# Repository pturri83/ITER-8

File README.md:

# DB6502 - Dawid Buchwald's 6502 Computer

This repository contains all the work in progress during my build of Ben Eater's inspired 6502 8-bit computer similar to typical machines of the early 1980s. If you haven't seen Ben's videos, I would strongly suggest you start there:

[Ben Eater's 6502 project](https://eater.net/6502)

As stated above, this build is not 100% compatible with what Ben had done - and for a reason, described in next section.

If I had to explain shortly "what it is", the answer would be: simple, yet easy to expand, 8-bit CPU based computer designed and built with one goal only: to use it as a learning and tinkering platform to understand how computers really work. You can use it for simple things like understanding buses, clock cycles, instruction execution, but it also demonstrates more complex concepts like interrupts, interfaces to external components and device handling. More on that below. Everything, hopefully, is simple enough to wrap your head around by one person in couple of weeks.

## Why build something different

[Ben's videos](https://www.youtube.com/playlist?list=PLowKtXNTBypFbtuVMUVXNR0z1mu7dp7eH) on 6502 computer are absolutely awesome - it's one of the best sources in the whole Internet explaining how any computer works. The build he introduced is probably sufficient for most of the things you might ever want to build, and yet I decided to deviate from his design.

The rationale behind this project is pretty simple - the best way to test your understanding of certain subject is to try to expand on what you have learned. You never know if you understood something until you test it by introducing changes to original design - and I used this approach in this project to learn a lot. It was my first proper electronics project, so I would like to apologize for any mistakes. If you think something is off or could have been done differently - please go ahead and raise issue for the repo! All improvements are welcome!

## Why would you bother using DB6502 instead of BE6502

Basically, it gives you almost all the flexibility of Ben's buid without the hassle of breadboard connections for the critical components. You can still run all of Ben's programs (using second VIA port), but the days of looking for loose wire between RAM and CPU are over :) You can, obviously, still experiment with peripherals and breadboard connections using extension port and second VIA.

On top of that you get additional features like extra screen (via onboard connector), keyboard for more versatile input and finally all-in-one serial over USB terminal. You also get easy to use software ready to be installed on the machine to jumpstart your tinkering. When using bootloader you don't even have to flash the EEPROM more than once!

**Important note:** All of the content here is, and always will be open source and free to use, and I don't intend to make any profit out of it. The only way I get anything at all (and it's only small commission to be used for future PCBWay orders) is when you order my boards from PCBWay using the links posted below, but you are welcome to grab these gerber files and order the boards from another provider, or even from PCBWay, just by uploading gerbers to your account, if you don't want me to get the commission :)

## What is different

Compared to Ben's 6502 build I introduced the following changes:

1. Added [automatic power-up reset circuitry](Schematics/README.md#automatic-power-on-reset),
2. Changed [address decoder logic](Schematics/README.md#address-decoder-change) (**very important from compatibility perspective**),
3. Changed [LCD interface](Schematics/README.md#lcd-interface-change) from 8-bit to 4-bit (**very important from compatibility perspective**),
4. Added [additional VIA chip](Schematics/README.md#extra-via-chip) to provide easy expansion of the system,
5. Added [ACIA chip for serial communication](Schematics/README.md#extra-acia-chip-for-serial-communication),
6. Added (**optional - more on that later**) [USB-UART interface](Schematics/README.md#extra-usb-uart-interface-chip) for easy connectivity with PC,
7. Added [PS/2 keyboard port and ATtiny4313-based keyboard controller](Schematics/README.md#ps2-keyboard-interface-and-attiny4313-based-controller) to provide proper replacement for five pushbuttons in Ben's design,
8. Added [expansion port](Schematics/README.md#expansion-port) (not really deviation from Ben's build, save for one detail - unlike Ben's build, my version can support various interrupt sources, including the expansion port),
9. Modified [clock module](Schematics/README.md#modified-clock-module) (external),
10. Changed [compilator from VASM to CC65](Schematics/README.md#migration-from-vasm-to-cc65),
11. Added [simple way to choose clock source](Schematics/README.md#clock-input).

You might be wondering if this means that you can't run Ben's programs on DB6502 - and the answer is **YES YOU CAN**. Indeed, some changes to the code are necessary, but thanks to the additional VIA chip and with some changes to the addressing mode you can run any program from Ben's videos. If you want to use LCD in 8-bit mode, you can also use the additional VIA for it, ignoring the built-in LCD connector.

By the way, the opposite is also true - **you can compile and run my programs on Ben's computer**. There are special compilation flags that enable usage of Ben's address decoder. I will describe this in more detail in software section.

Detailed description and rationale for each change is discussed in [Schematics README](Schematics/README.md).

## Getting started

Okay, so it should be pretty clear what this project is about, so how to start playing with it? That really depends on what you decide to do:

- Stick with BE6502 and just use subset of provided software (either to install it in EEPROM, or just use it as reference for your own hacking),
- Build your own breadboard design based on this one with any modifications you can think of,
- Order PCBs of DB6502, solder the components and run provided software to see how it works and get started with your own designs.

To start from scratch it's actually easiest to select last option - after some waiting you will end up having pretty solid base to extend your design on.

### Using provided software with BE6502

If you decide to go down that route, head straight to the `Software` folder, where you will find several programs either identical or similar to what Ben has shown in his videos, but built with much more versatile toolchain.

If you want to read more, go ahead and read [Software folder](Software/README.md) section. Make sure to check out the [building software](Software/README.md#building-software) subsection, as it explains how to compile programs to run on BE6502 directly.

### Build your own breadboard design

Maybe you have already started expanding on Ben's build, or maybe you are just considering it now. If you want to check out how I did certain things, jump right into `Schematics` [folder](Schematics/README.md), where you will find KiCAD projects for all the components used in this project. Obviously the most important one is the `65C02_Computer` project, but there are some additional goodies there.

**Please note:** This part is not very well documented, I have assumed that anybody willing to dig into these schematics already knows how to read them.

Most of the decisions made during the schematic design were explained above. Justification for anything not covered here can be probably found in the [invaluable 6502 primer](http://wilsonminesco.com/6502primer/).

### Using my PCB design

This will be explained in the most detail, obviously. Start with getting [the PCBs](Schematics/README.md#ordering-pcb). **Please note:** clock module is entirely optional, but really useful for single stepping or slow clocking required by Ben Eater's design of Arduino Mega based bus analyzer. As explained in number of places here, you can either order PCBs from PCBWay directly or use your manufacturer of choice - it should have no impact on the final result.

## What's in the repo

Everything, basically. Schematics of the 6502 board, modified clock module, address decoder and other circuits I built during the project. Arduino sketches I used for debugging and simple programs used to test different features.

And, last but not least, full set of sample programs to follow Ben's videos on DB6502 plus my own bootloader/OS. The last two things are coming soon :)

### `Arduino` folder

There are several sketches there, and their full description is available is [separate README](Arduino/README.md).

### `AVR` folder

There are several projects there, used to experiment with pure `avr-gcc` development for Atmel AVR chips. While it has been interesting adventure that I plan to explore further in the future, it was easier to stick to standard Arduino tools for now and simply restructure code to work there.

### `Datasheets` folder

All the datasheets I used when designing DB6502, attached for reference.

### `Schematics` folder

All the KiCAD schematics for the 6502 computer, modified clock module and several others:

- 65C02_Computer - main schematic, including PCB design for DB6502 computer,
- Clock_module - schematic for the modified clock module, including PCB design,
- 555_troubleshoot - schematic of circuit used in [troubleshooting of clock module monostable noise issue](https://www.reddit.com/r/beneater/comments/edp1ls/noise_issue_in_monostable_mode_of_ben_eaters/),
- Address_decoder_basic - schematic of Ben Eater's address decoder for 6502 project,
- Address_decoder_basic_v2 - slightly modified version of the above,
- Address_decoder_extended - schematic of my own address decoder, used in the DB6502 computer.

There is dedicated [README](Schematics/README.md) in the folder, containing all the build-related details.

### `Software` folder

This one is the most important folder, as it contains range of different programs to play with the 6502 computer. Large subset of this programs can be built for Ben Eater's version of the 6502 computer without any changes. Some of them, however, use features available only in DB6502, like ACIA or keyboard connector. These can still be ran on Ben Eater's 6502 computer, assuming that compatible hardware is added to it.

The `Software` folder is currently divided into four main parts:

- `build` - temporary folder where all the build artifacts are created, including ROM binaries to be uploaded to EEPROM,
- `common` - common sources: include files with common constants, sources with shared function, configuration files for different address decoder logic modes, shared makefile used by all projects and small python script to optimize size of loadable modules,
- `rom` - set of projects used to create various ROM images to follow Ben's videos, test different features of the board and **some day** complete operating system for the computer,
- `load` - set of project containing loadable modules. These can be uploaded at runtime, without the need to flash the EEPROM. Basic bootloader is required, obviously, and the usage instructions are provided below.

There is also one "master" makefile located directly in the `Software` folder - it will build all the projects in `rom` and `load` subfolders.

There is dedicated [README](Software/README.md) in the folder, containing all the software-related details.

## Credits

This project would not be possible if not inspiration, support and help from many, many people:

- [Ben Eater](https://eater.net) - his videos inspired me to learn all this,
- [Dirk Grappendorf](https://grappendorf.net) - awesome documentation of his own 6502 project,
- [Wilson Mines Co.](http://wilsonminesco.com) - the best source of 6502-related information,
- [Dane Creek Photography](https://github.com/danecreekphotography) - for all his support and test driving the project,
- [u/transistorykris](https://www.reddit.com/user/transitorykris/) - his [KrisOS](https://github.com/transitorykris/krisos) is a great inspiration for my own OS development,
- [r/beneater community](https://www.reddit.com/r/beneater/) - for all the great ideas, feedback, creative spirit and exceptional support.

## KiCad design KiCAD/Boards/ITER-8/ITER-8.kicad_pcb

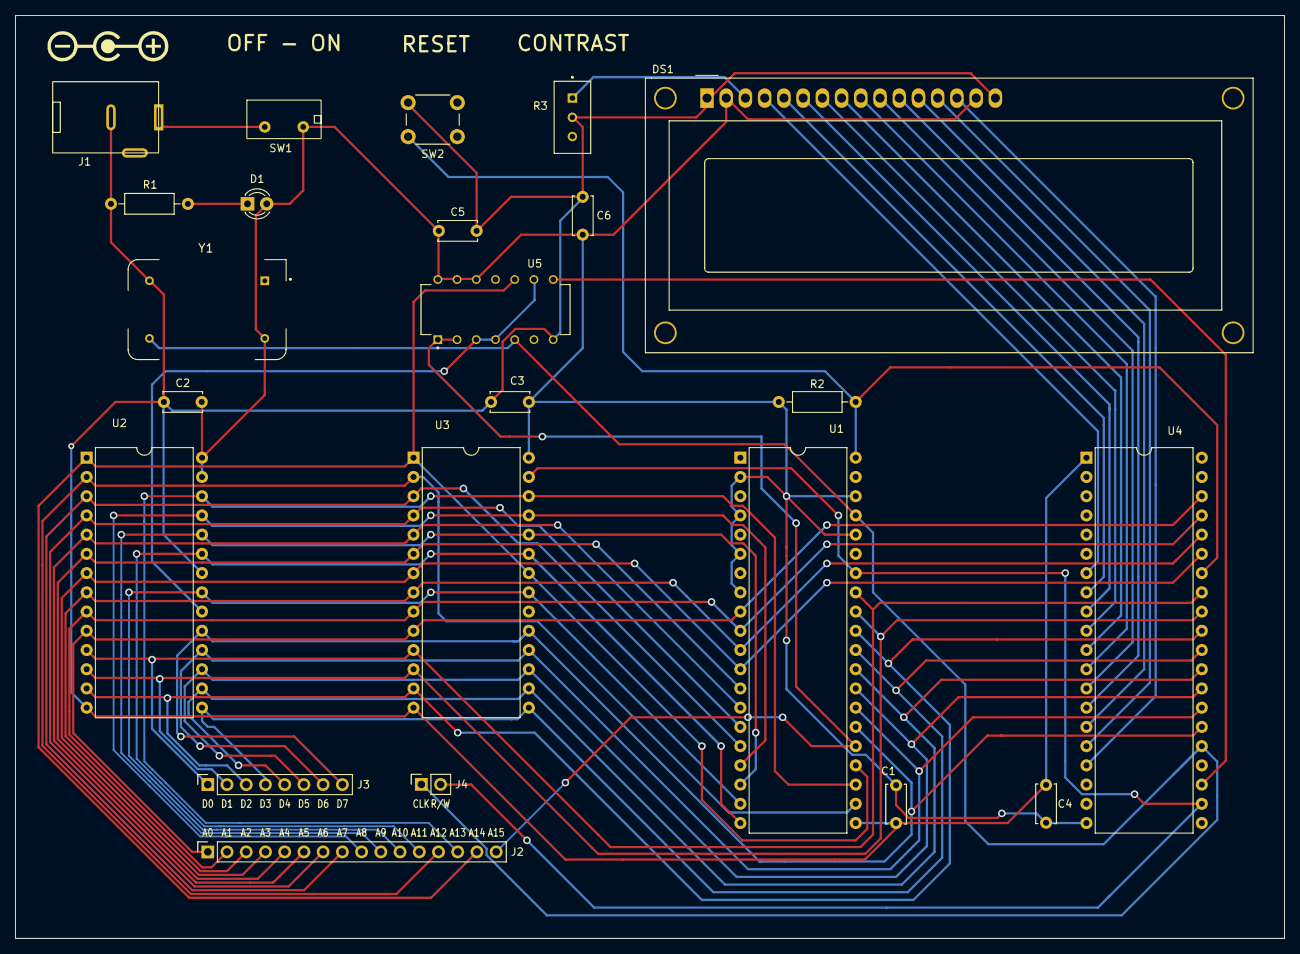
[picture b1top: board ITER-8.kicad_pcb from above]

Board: 2 copper layers, 167.6 x 121.9 mm, 23 parts (0 on the bottom side), 46 nets.

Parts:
C1, C2, C3, C4, C5, C6: 100n; C_Disc_D5.0mm_W2.5mm_P5.00mm
D1: LED; LED_D3.0mm
DS1: LCD-016M002B; WC1602A
J1: DC-005
J2: Conn_01x16; PinSocket_1x16_P2.54mm_Vertical
J3: Conn_01x08; PinSocket_1x08_P2.54mm_Vertical
J4: Conn_01x02; PinSocket_1x02_P2.54mm_Vertical
R1: 150R; R_Axial_DIN0207_L6.3mm_D2.5mm_P10.16mm_Horizontal
R2: 1k; R_Axial_DIN0207_L6.3mm_D2.5mm_P10.16mm_Horizontal
R3: 3296-W; TRIM_3296-W
SW1: A11JP
SW2: Dual Push Button; SW_PUSH_double_6mm
U1: W65C02S6TPG-14; DIP-40_W15.24mm
U2: AT28C256-15PU; DIP-28_W15.24mm
U3: AS6C62256-55PCN; DIP-28_W15.24mm
U4: W65C22SxP; DIP-40_W15.24mm
U5: SN74HC00N; DIP794W45P254L1969H508Q14
Y1: ECS-100AX-010; OSC_ECS-100AX-010

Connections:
+5V: J1.1, SW1.1 (A)
/A0: J2.1, U1.9 (A0), U2.10 (A0), U3.10 (A0), U4.38 (RS0)
/A1: J2.2, U1.10 (A1), U2.9 (A1), U3.9 (A1), U4.37 (RS1)
/A2: J2.3, U1.11 (A2), U2.8 (A2), U3.8 (A2), U4.36 (RS2)
/A3: J2.4, U1.12 (A3), U2.7 (A3), U3.7 (A3), U4.35 (RS3)
/A4: J2.5, U1.13 (A4), U2.6 (A4), U3.6 (A4)
/A5: J2.6, U1.14 (A5), U2.5 (A5), U3.5 (A5)
/A6: J2.7, U1.15 (A6), U2.4 (A6), U3.4 (A6)
/A7: J2.8, U1.16 (A7), U2.3 (A7), U3.3 (A7)
/A8: J2.9, U1.17 (A8), U2.25 (A8), U3.25 (A8)
/A9: J2.10, U1.18 (A9), U2.24 (A9), U3.24 (A9)
/A10: J2.11, U1.19 (A10), U2.21 (A10), U3.21 (A10)
/A11: J2.12, U1.20 (A11), U2.23 (A11), U3.23 (A11)
/A12: J2.13, U1.22 (A12), U2.2 (A12), U3.2 (A12)
/A13: J2.14, U1.23 (A13), U2.26 (A13), U3.26 (A13), U4.24 (CS1)
/A14: J2.15, U1.24 (A14), U2.1 (A14), U3.1 (A14), U3.22 (~OE), U5.10 (3B)
/A15: J2.16, U1.25 (A15), U5.1 (1A), U5.2 (1B)
/D0: J3.1, U1.33 (D0), U2.11 (D0), U3.11 (Q0), U4.33 (D0)
/D1: J3.2, U1.32 (D1), U2.12 (D1), U3.12 (Q1), U4.32 (D1)
/D2: J3.3, U1.31 (D2), U2.13 (D2), U3.13 (Q2), U4.31 (D2)
/D3: J3.4, U1.30 (D3), U2.15 (D3), U3.15 (Q3), U4.30 (D3)
/D4: J3.5, U1.29 (D4), U2.16 (D4), U3.16 (Q4), U4.29 (D4)
/D5: J3.6, U1.28 (D5), U2.17 (D5), U3.17 (Q5), U4.28 (D5)
/D6: J3.7, U1.27 (D6), U2.18 (D6), U3.18 (Q6), U4.27 (D6)
/D7: J3.8, U1.26 (D7), U2.19 (D7), U3.19 (Q7), U4.26 (D7)
/PA5: DS1.4 (RS), U4.7 (PA5)
/PA6: DS1.5 (R/W), U4.8 (PA6)
/PA7: DS1.6 (E), U4.9 (PA7)
/PB0: DS1.7 (D0), U4.10 (PB0)
/PB1: DS1.8 (D1), U4.11 (PB1)
/PB2: DS1.9 (D2), U4.12 (PB2)
/PB3: DS1.10 (D3), U4.13 (PB3)
/PB4: DS1.11 (D4), U4.14 (PB4)
/PB5: DS1.12 (D5), U4.15 (PB5)
/PB6: DS1.13 (D6), U4.16 (PB6)
/PB7: DS1.14 (D7), U4.17 (PB7)
GND: C1.1, C2.1, C3.1, C4.1, C5.2, C6.2, DS1.1 (VSS), DS1.16 (LED(-)), J1.2, R1.1, R3.2, SW2.2, U1.21 (VSS), U2.14 (GND), U2.22 (~OE), U3.14 (GND), U4.1 (VSS), U5.7 (GND), Y1.7 (CASE_GND)
unnamed: C1.2, C2.2, C3.2, C4.2, C5.1, C6.1, D1.2 (A), DS1.2 (VDD), DS1.15 (LED(+)), R2.1, SW1.2 (B), U1.2 (RDY), U1.4 (~IRQ), U1.6 (~NMI), U1.8 (VDD), U1.36 (BE), U1.38 (~SO), U2.27 (~WE), U2.28 (VCC), U3.28 (VCC), U4.20 (VCC), U5.12 (4A), U5.13 (4B), U5.14 (VCC), Y1.14 (+VDC)
unnamed: D1.1 (K), R1.2
unnamed: DS1.3 (VO), R3.1
unnamed: J4.1, U1.37 (ϕ0), U4.25 (ϕ2), U5.5 (2B), Y1.8 (OUTPUT)
unnamed: J4.2, U1.34 (R/~W), U3.27 (~WE), U4.22 (R/~W)
unnamed: R2.2, SW2.1, U1.40 (~RES), U4.34 (~RES)
unnamed: U2.20 (~CS), U5.3 (1Y), U5.4 (2A), U5.9 (3A)
unnamed: U3.20 (~CS), U5.6 (2Y)
unnamed: U4.23 (~CS2), U5.8 (3Y)

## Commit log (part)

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2023-11-18 Test 1 & 2
    First and second test roms, with related scripts, diagrams, and layouts.
2023-11-30 4-bit LCD
    LCD in 4-bit mode, including assembly subroutines for timings. New test of the division with remainder.
2023-12-08 Button interrupt
    New test to count the number of interrupts from a push button. The power section has been changed to automatically reset the computer.
